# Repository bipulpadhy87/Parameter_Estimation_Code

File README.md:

# Complex-receiver inductance estimator

Revision: 2026-09-26

**Before enabling identification, set the actual installed primary and
secondary compensation capacitances.** Both remain `0UL` by default, as in the
supplied firmware; zero capacitance intentionally prevents a valid result.
Do not substitute the simulation's values for hardware measurements.

Also enter/verify the actual primary bridge voltage, effective series losses,
coil-inductance bounds, phase calibration, and uncertainty allowances. The
inherited voltage default is 5000 mV; the inherited resistance defaults are
zero. None of these defaults is a measurement of the hardware.

The numerical core uses `long double` for the slow solve. TI documents this as
64-bit for both C28x COFF and EABI; plain `double` is only 32-bit in COFF. Allow
64-bit floating-point operations in the CCS compiler settings (do not retain
`--float_operations_allowed=none` or `=32` for this translation unit). Keep
strict floating-point semantics for the NaN/finite checks. The C28x runtime
support library supplies the arithmetic. No MATLAB runtime, heap allocation,
complex-number library, or external numerical library is required.

The larger matrices use static storage. The solver is not reentrant and must
not run in an ISR. It executes in the existing paused-acquisition analysis
path after both records are collected. Primary PWM continues as before during
analysis. **Target execution time, stack/RAM/flash use, watchdog servicing and
protection behavior have NOT been measured.** Check the CCS map and profiling
results, and preserve independent hardware protection before a power test.
Start validation with appropriate low-energy, current-limited conditions;
the parameter estimator is not a protection function.

TI references for the numeric implementation:
- https://software-dl.ti.com/docs/esd/SPRU514/c28x-double-and-long-double-floating-point-types-spru5144178.html
- https://software-dl.ti.com/C2000/docs/optimization_guide/phase1/floating_point.html

## Which uploaded method was used

The basis is `parameterestimation.m` from `Parameter estimation.zip`.
An unmodified copy is included as `reference/parameterestimation_original.m`.
That script uses two **fundamental** input impedances to estimate four real
unknowns: common self-inductance L, mutual inductance M, receiver resistance Req,
and receiver reactance Xeq. Its later calculation of DC load resistance still
uses `pi^2/8`, and its DC-current calculation uses `2/pi`.

This package ports the complex-load approach and its analytic quadratic seeds,
**but does not port those DC conversions**. To retain the user's requirement
that the third harmonic participate in identification, it extends the model
to a second, independent complex receiver ratio at the third harmonic.
That extension and the multistart nonlinear optimizer are new work; they are
not an assertion that the uploaded MATLAB script already implemented them.

The alternative `doublefdoublepulse.m` was not used as the estimator core. Its
`f9_dual_asym` enforces a secondary-current zero at a phase derived from receiver
voltage and later uses bridge-waveform voltage/current conversions. Those
constraints are not appropriate for an arbitrary synchronous switching law.
`Lpestimation.m` likewise has a virtual-short assumption for its unsensed
receiver case and optional secondary measurements. No Simulink model in the
ZIP was executed or changed.

## Model and the four input impedances

The four observations, in code order, are

    Zin1(f0), Zin1(f1), Zin3(f0), Zin3(f1).

For harmonic h at operating point j:

    omega_hj = h * 2*pi * f_j
    Zp_hj = Rp + j*(omega_hj*L - 1/(omega_hj*Cp))
    Zs_hj = Rs + j*(omega_hj*L - 1/(omega_hj*Cs))
    Zin_hj = Zp_hj + (omega_hj*M)^2 / (Zs_hj + Zrec_h).

The independent fitted parameters are

    L, |M|, Rrec1, Xrec1, Rrec3, Xrec3.
    Zrec1 = Rrec1 + j*Xrec1
    Zrec3 = Rrec3 + j*Xrec3

There are eight measured real components and six fitted real parameters.
Zrec1 need not equal Zrec3. Rrec3 can be negative: these are terminal phasor
ratios under switching operation, not four independent passive linear loads.
A negative apparent third-harmonic resistance is not itself a fault.
Fundamental receiver resistance is constrained to be nonnegative; reverse
power-flow operation is outside this version.

**This model is rectifier-type independent, not assumption-free.** It can be
applied to diode or synchronous receivers when the following conditions hold:

1. For each harmonic separately, the receiver terminal ratio stays
   approximately constant between the two test frequencies:

       Zrec1(f0) approximately equals Zrec1(f1)
       Zrec3(f0) approximately equals Zrec3(f1).

   This is the essential restriction that makes identification possible.
   It is not the assumption Zrec1 = Zrec3. A receiver controller, DC voltage,
   conduction pattern or load change can violate it. The default inherited
   85/100 kHz pair is NOT certified to satisfy this restriction. Check it
   experimentally or in a trustworthy full switching model. A smaller
   frequency gap may reduce model drift but also worsens identifiability.

2. The resonant network is series-series; Lp=Ls=L. Known Cp, Cs, Rp and Rs must
   describe the actual paths. The supplied constant-loss model neglects
   frequency-dependent losses beyond those constants.

3. L and M are stable across both records and harmonics. Saturation, appreciable
   motion during collection, or changing coil geometry can violate this.

4. Input voltage/current phasors are correctly calibrated and time-aligned,
   both records are in periodic steady state, and both harmonics are strong
   enough to be measured. Receiver harmonic frequency conversion is NOT
   represented by a general harmonic-transfer matrix.

Residual and ambiguity checks cannot detect every possible model violation:
a changed receiver can sometimes imitate different coil parameters. A low
residual or a valid flag is not proof of physical truth. No claim is made that
this works for every possible synchronous controller or diode conduction mode.

## Numerical implementation

The source-script quadratic is retained for initialization, once per harmonic.
Let W=omega*1e-6 so L and M are expressed in microhenries, and let

    D_j = Re(Zin_j) - Rp
    C_j = Im(Zin_j) + 1/(omega_j*Cp)
    K = (W0/W1)^2.

Then the source's constant-complex-load constraint gives

    a = W0^2*(D0-D1)
    b = 2*(D1*W0*C0 - D0*W0^2*C1/W1)
    c = K*D0*(D1^2+C1^2) - D1*(D0^2+C0^2)
    a*L^2 + b*L + c = 0.

All in-range roots are retained. The code does not choose the first positive
root or silently return a nominal inductance when inversion fails. Near-linear
quadratics are handled separately; a cancellation-resistant quadratic formula
is used for ordinary roots.

Additional bounded grid seeds come from eliminating the receiver ratios:

    F_hj = Zin_hj - Zp_hj(L)
    A_hj = W_hj^2/F_hj
    t = M_uH^2
    Zrec_hj = t*A_hj - Zs_hj(L).

Equal receiver ratios across the frequency pair require

    t*(A_h0-A_h1) = j*(Xs_h0-Xs_h1).

A weighted least-squares solution for real t initializes M. The two
reconstructed ratios initialize each harmonic's load. These are only seeds.
The final damped Gauss-Newton iterations minimize the **forward input-impedance
errors**, using all eight real/imaginary components and analytic derivatives.

The search is finite multistart optimization, not a certified global search.
It compares materially different found candidates, rejects bound-limited or
locally weak results, and returns numerical diagnostics. It cannot prove
that an unsearched alternative solution does not exist.

## Measurement uncertainty and thresholds

The adapter computes an engineering allowance for each complex observation:

    sigma_Z = absolute_floor + relative_allowance*abs(Z)
              + sqrt(sigma_V^2 + abs(Z)^2*sigma_I^2)/abs(I).

These are editable settings in `psfbpcmc_user_settings.h`. The supplied defaults
are starting allowances, not characterized ADC/sensor statistics. The
linearized L/M sensitivity is obtained from the local weighted Jacobian and
these allowances; it is not a guaranteed accuracy or confidence interval.
Systematic phase, winding-loss, capacitance and model errors are not fully
represented by these numbers. Do not enlarge allowances simply to suppress
faults or to force an estimate to be accepted.

Default checks include normalized residual RMS <= 3, relative L/M sensitivity
<= 20%, and the inherited additional absolute residual ceiling of 5 ohms.
A second found candidate within four normalized squared-error units and
separated by over 1% in L or 2% in M triggers the ambiguity flag. These are
engineering acceptance rules, not universal statistical thresholds.

## CCS Expressions / outputs

Always inspect `WPT_identificationValid` before using the fitted values.
The solver can expose a rejected candidate's values for diagnosis; they are
not valid measurements when that flag is zero.

| Variable | Meaning / units |
|---|---|
| `WPT_estimatedSelfInductanceNanoHenry` | Common Lp=Ls, nH |
| `WPT_estimatedMutualInductanceNanoHenry` | Magnitude of M, nH |
| `WPT_estimatedCouplingPermille` | 1000*abs(M)/L |
| `WPT_estimatedEquivalentAcLoadMilliOhm` | Fundamental Rrec1, mOhm; legacy name retained |
| `WPT_estimatedEquivalentAcReactanceMilliOhm` | Fundamental Xrec1, signed mOhm |
| `WPT_estimatedThirdAcResistanceMilliOhm` | Third-harmonic Rrec3, signed mOhm |
| `WPT_estimatedThirdAcReactanceMilliOhm` | Third-harmonic Xrec3, signed mOhm |
| `WPT_identificationResidualMilliOhm` | Unweighted RMS across eight components, mOhm |
| `WPT_identificationNormalizedResidualPermille` | 1000 * weighted RMS |
| `WPT_identificationLRelativeSensitivityPermille` | 1000 * local relative L sensitivity |
| `WPT_identificationMRelativeSensitivityPermille` | 1000 * local relative M sensitivity |
| `WPT_identificationImpedanceSigmaMilliOhm[4]` | Per-observation engineering uncertainty, mOhm |
| `WPT_identificationSolverFlags` | Bitmask described below; 0 means checks passed |
| `WPT_identificationSolutionsChecked` | Number of multistart results checked |
| `WPT_identificationAlternativeSelfInductanceNanoHenry` | Found alternative L when ambiguous |
| `WPT_identificationAlternativeMutualInductanceNanoHenry` | Found alternative M when ambiguous |
| `WPT_identificationModelWarning` | Stays 1 after every solve: modeling assumptions remain |
| `WPT_estimatedDcLoadValid` | Always 0; no DC load estimate is available |
| `WPT_estimatedDcLoadMilliOhm` | Always invalid sentinel 0xFFFFFFFF, never a resistance |

Flag bits may be combined:

| Bit value | Meaning |
|---:|---|
| 1 | Invalid configuration/input |
| 2 | No physically acceptable seeded solution |
| 4 | Excessive fit residual |
| 8 | Materially different, similarly compatible solutions found |
| 16 | Weak local L/M identifiability or singular sensitivity calculation |
| 32 | Result at an inductance/coupling bound |
| 64 | Required third-harmonic record missing |
| 128 | Invalid/too-small phasor or guarded arithmetic range |

Set `WPT_identificationResetRequest=1` to start another experiment, as before.
Read the two existing input-impedance arrays for the fundamental and the two
third-harmonic arrays to see the actual four observations supplied to the fit.
No secondary current sensor or secondary telemetry was added.

## PWM, dead time and acquisition

The existing acquisition rate, ADC configuration, harmonic extraction,
automatic case-7 to case-5 transition, PWM setup, phase values, blanking, and
trip handling are retained. In particular, case 7 retains **PH_1_4=586**.
Seventeen existing functions were compared after removing comments and
whitespace; their executable source is unchanged.

Primary voltage reconstruction still uses actual configured PWM timing,
primary dead time and current-dependent clamp polarity. The only executable
change in that reconstruction function permits zero source V3 when a usable
I3 is present; it no longer unnecessarily rejects that observation. The
dead-time arithmetic itself is unchanged.

That voltage reconstruction still neglects Coss, driver propagation delays,
diodes' finite voltage drops and ringing. Measured primary voltage phasor
overrides remain available. No receiver-side PWM phase or diode waveform is
used to calculate the receiver ratios.

## Validation actually performed

These checks are included as code/results in `tests/`:

- Estimator core compiled with GCC C99, `-Wall -Wextra -Werror`, using host
  long double and an explicit 64-bit double configuration.
- Five noiseless synthetic model cases: resistive fundamental load, reactive
  load, negative third-harmonic resistance, strong coupling, and different
  fundamental/third loads. Parameter recovery matched the constructed models
  to numerical precision. This is algebra/software validation, not evidence
  about a real rectifier.
- Analytic Jacobian checked against independent NumPy finite differences.
- Invalid capacitance/frequency/noise settings, NaNs, weak coupling, selected
  receiver changes and corrupt observations tested. Rejected results clear
  stale valid outputs. This does not claim all receiver changes are detectable.
- Forty randomized exact-model cases and forty noisy cases with fixed seed
  260926. All passed the stated test assertions. In the noisy test, each
  impedance component had 0.01-ohm Gaussian noise and the largest L/M errors
  were approximately 0.157% / 0.209% for that one chosen synthetic system.
- The same core tests ran under GCC's undefined-behavior sanitizer.
- The actual new adapter was extracted from the revised main.c and compiled
  with the actual updated settings/header. With quantized synthetic mV/mA
  phasors, true L=180 uH and M=130 uH produced L=179.799 uH and M=129.783 uH;
  the input-impedance RMS residual was 44 mOhm. DC validity stayed false.
- Default zero capacitor settings, missing third data, zero third current,
  oversized phasors and repeated frequencies failed closed in adapter tests.
- Regression comparison confirmed the preserved executable functions and
  case-7 phase correction.

**NOT performed:** full TI CCS compilation/linking, real-time timing or stack
profiling on the F280049C, MATLAB/Simulink execution, time-domain diode or
synchronous-rectifier simulation, sensor calibration, or hardware testing.
Do not interpret the synthetic tests as verification of arbitrary receivers.

To rerun the portable tests, install Python 3, NumPy and a C99 GCC compiler:

    python tests/test_estimator.py
    python tests/test_integration.py
    python tests/test_extended.py

The preservation test additionally needs the unmodified pre-change firmware:

    python tests/test_preservation.py /path/to/original/directory

Test binaries are intentionally not included. Generated `tests/build/` files
are host-test artifacts, not CCS project sources.

## Package contents

The three firmware files are at the package root. Two unified `.patch` files
show changes against the supplied original main/settings files. `reference/`
contains the unmodified chosen MATLAB script. `tests/` contains test sources
and recorded JSON results. No source Library file or original ZIP was modified.

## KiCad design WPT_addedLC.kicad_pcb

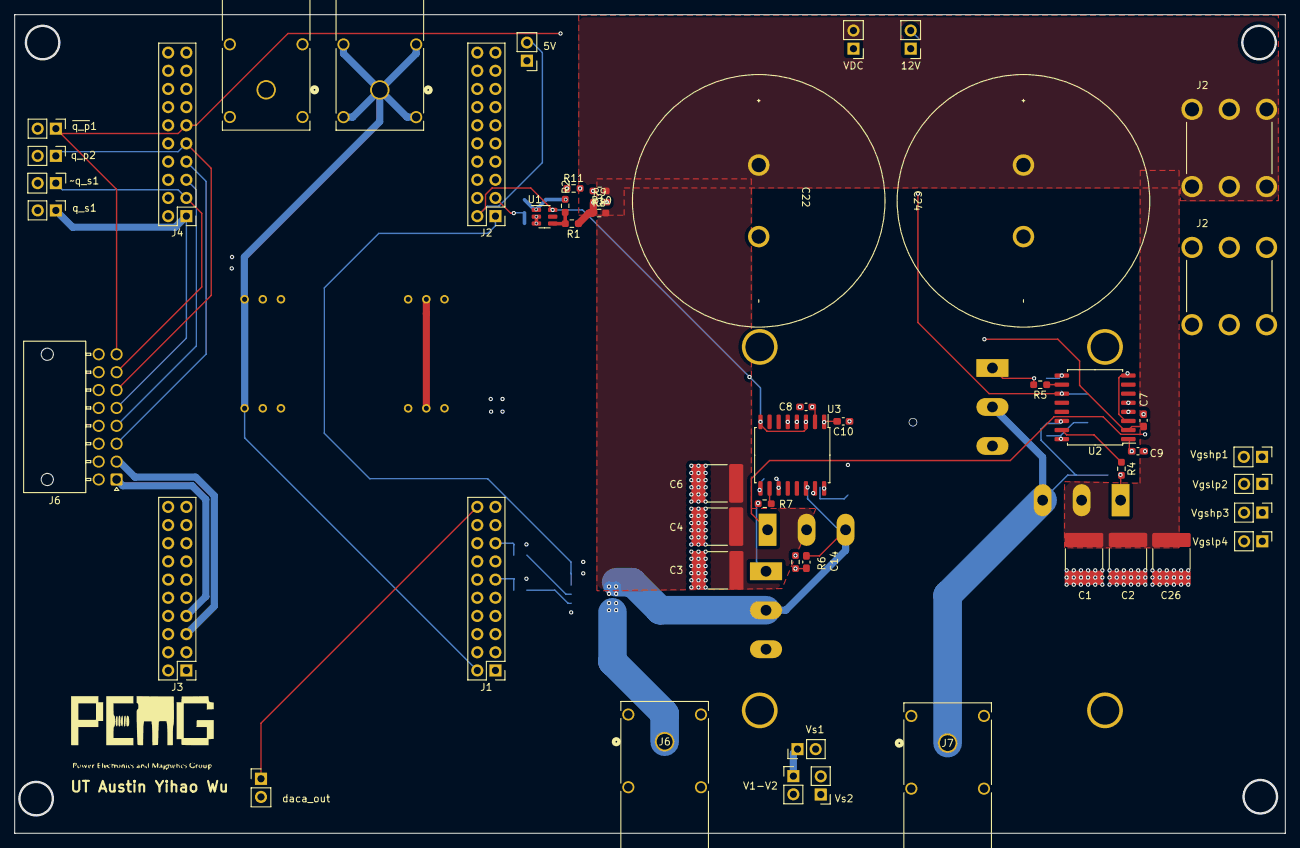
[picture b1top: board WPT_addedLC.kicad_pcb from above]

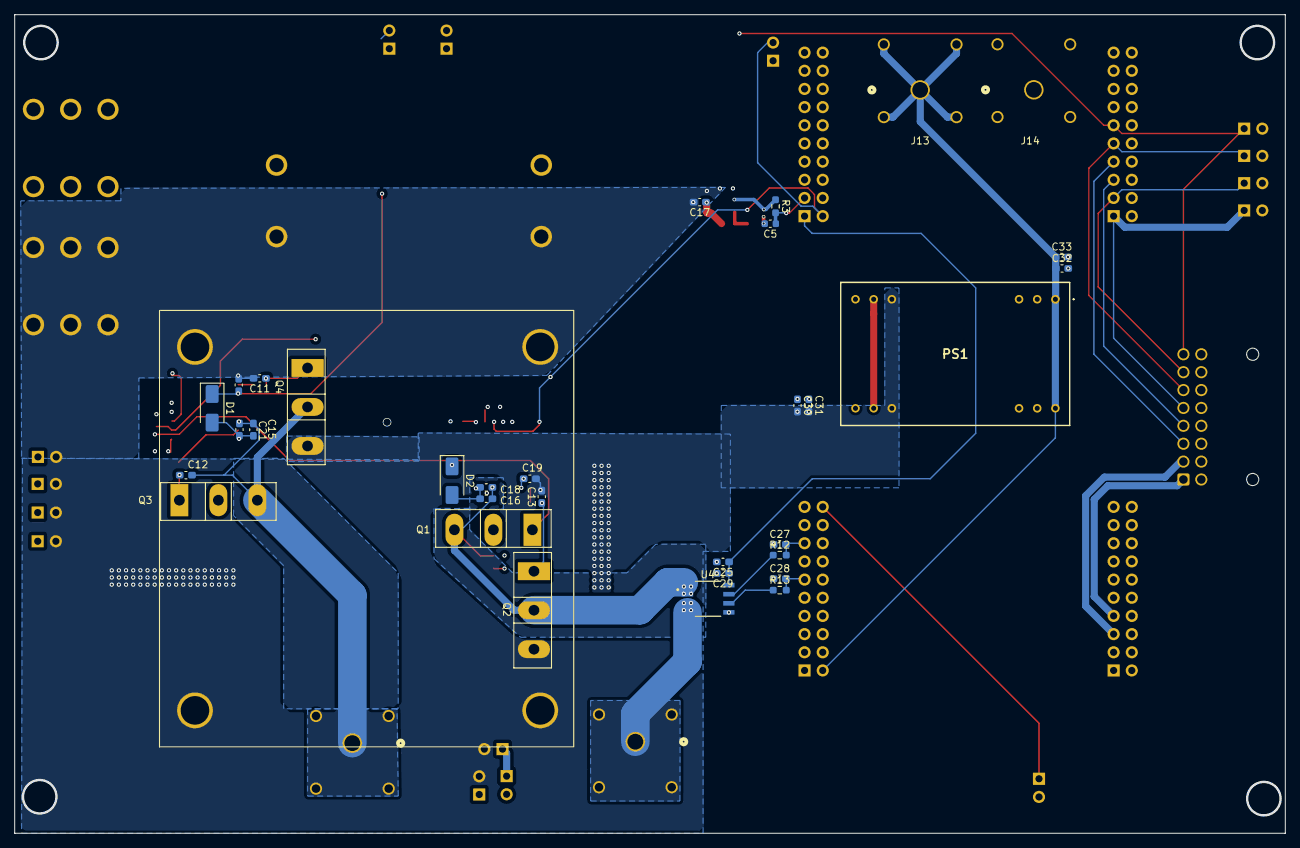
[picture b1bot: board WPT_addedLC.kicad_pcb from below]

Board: 4 copper layers, 177.6 x 114.4 mm, 80 parts (30 on the bottom side), 36 nets.

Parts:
5V, 12V: TP_Header; PinHeader_1x02_P2.54mm_Vertical
C1, C2, C3, C4, C6, C26: C_Small; C_2220_5750Metric_Pad1.97x5.40mm_HandSolder
C5: 1nf; C_0603_1608Metric
C7, C8, C9, C10, C11, C12, C13, C14, C15, C16, C17, C18, C19, C20, C21: C_Small; C_0603_1608Metric_Pad1.08x0.95mm_HandSolder
C22, C24: 1mF; CP_Elec_dia1in
C25, C31, C32: 0.1u; C_0603_1608Metric_Pad1.08x0.95mm_HandSolder
C27, C28: 100p; C_0603_1608Metric_Pad1.08x0.95mm_HandSolder
C29, C30, C33: 1u; C_0603_1608Metric_Pad1.08x0.95mm_HandSolder
D1, D2: D_SMA
J1, J2#2, J3, J4: Conn_02x10_Row_Letter_First; PinHeader_2x10_P2.54mm_Vertical_LetterNumber
J2, J2#3: Conn_01x01_Pin; KEYSTONE_7808
J6, J7, J13, J14: FCR7350R; CONN1_FCR7350R_CLF
J6#2: Conn_02x08_Odd_Even; Molex_Nano-Fit_105314-xx16_2x08_P2.50mm_Horizontal
PS1: TEL_3-0512; TEL30522
Q1, Q2, Q3, Q4: C3M0065090D; TO-247-3_Vertical
R1, R2, R8, R9, R10, R11: 10k7; R_0603_1608Metric_Pad0.98x0.95mm_HandSolder
R3: 100; R_0603_1608Metric_Pad0.98x0.95mm_HandSolder
R4, R5, R6, R7: 10; R_0603_1608Metric_Pad0.98x0.95mm_HandSolder
R12, R13: 49.9; R_0603_1608Metric_Pad0.98x0.95mm_HandSolder
U1: TLV2470; SOT-23-6
U2, U3: ADuM3223; SOIC-16W_7.5x10.3mm_P1.27mm
U4: ACS37030LLZATR-020B3; IC_ACS37030LLZATR-020B3
V1-V2: TP_Header; PinHeader_1x02_P2.54mm_Vertical
VDC: TP_Header; PinHeader_1x02_P2.54mm_Vertical
Vgshp1, Vgshp3: TP_Header; PinHeader_1x02_P2.54mm_Vertical
Vgslp2, Vgslp4: TP_Header; PinHeader_1x02_P2.54mm_Vertical
Vs1, Vs2: TP_Header; PinHeader_1x02_P2.54mm_Vertical
daca_out: TP_Header; PinHeader_1x02_P2.54mm_Vertical
q_p2: TP_Header; PinHeader_1x02_P2.54mm_Vertical
q_s1: TP_Header; PinHeader_1x02_P2.54mm_Vertical

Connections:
/3.3V: C25.1, C29.1, J2#2.a1, U4.6 (VDD)
/5V_uC: 5V.2, C32.1, C33.1, J1.b1, J2#2.b1, J13.1 (1_1), J13.2, J13.3, J13.4, J13.5, PS1.1 (+VIN_(VCC)_1), PS1.24 (+VIN_(VCC)_2), U1.6 (VDD), U2.3 (VDD1), U2.8 (VDD1), U3.3 (VDD1), U3.8 (VDD1)
/+12V: 12V.2, C19.1, C20.1, C30.1, C31.1, D1.1 (A), D2.1 (A), PS1.11 (+VOUT_1), PS1.14 (+VOUT_2), U2.11 (V_{DDB}), U3.11 (V_{DDB})
/Iout2_adc: C28.2, J1.a6, R13.2
/Iout_adc: C27.2, J1.a8, R12.2
/Vcurrent2: J6.1 (1_1), J6.2, J6.3, J6.4, J6.5, U4.2 (IP-)
/Vdc: C1.1, C2.1, C3.1, C4.1, C6.1, C22.1, C24.1, C26.1, J2#3.1_1, J2#3.1_2, J2#3.1_3, J2#3.1_4, J2#3.1_5, J2#3.1_6, Q1.2 (D), Q3.2 (D), R8.2, R10.2, VDC.2
/Vgshp1: C14.1, Q1.1 (G), R6.2, Vgshp1.1
/Vgshp3: C12.1, Q3.1 (G), R4.2, Vgshp3.1
/Vgslp2: C13.1, Q2.1 (G), R7.2, Vgslp2.1
/Vgslp4: C11.1, Q4.1 (G), R5.2, Vgslp4.1
/Vout_adc: C5.1, J2#2.a2, R3.2
/Vout_low: C17.1, R1.1, R8.1, R9.2
/Vs1: C14.2, C16.2, C18.1, Q1.3 (S), Q2.2 (D), U3.14 (GND_{A}), U4.1 (IP+), V1-V2.1, Vs1.1
/Vs2: C12.2, C15.2, C21.1, J7.1 (1_1), J7.2, J7.3, J7.4, J7.5, Q3.3 (S), Q4.2 (D), U2.14 (GND_{A}), V1-V2.2, Vs2.1
/daca_out: J1.b10, daca_out.1
/q_p: C9.2, J4.a5, J6#2.6, U2.1 (V_{1A}), q_p2.1
/q_s: C10.2, J4.a1, J6#2.5, U3.1 (V_{1A}), q_s1.1
/q_sh1: J4.a3, J6#2.4
/q_sh2: J3.a3, J6#2.2
/~q_p: C7.1, J4.a6, J6#2.8, U2.2 (V_{IB})
/~q_sh1: J4.a4, J6#2.3
/~q_sh2: J3.a4, J6#2.1
/~q_s: C8.1, J4.a2, J6#2.7, U3.2 (V_{IB})
Earth: 12V.1, C1.2, C2.2, C3.2, C4.2, C6.2, C11.2, C13.2, C17.2, C19.2, C20.2, C22.2, C24.2, C26.2, C30.2, C31.2, J2.1_1, J2.1_2, J2.1_3, J2.1_4, J2.1_5, J2.1_6, PS1.10 (COMMON_2), PS1.15 (COMMON_3), Q2.3 (S), Q4.3 (S), R9.1, R10.1, R11.2, U2.9 (GND_{B}), U3.9 (GND_{B}), VDC.1, Vgshp1.2, Vgshp3.2, Vgslp2.2, Vgslp4.2, Vs1.2, Vs2.2
GND: 5V.1, C5.2, C7.2, C8.2, C9.1, C10.1, C25.2, C27.1, C28.1, C29.2, C32.2, C33.2, J1.a5, J1.a7, J1.b2, J1.b5, J1.b6, J1.b7, J2#2.b2, J3.b1, J4.b1, J6#2.9, J6#2.10, J6#2.11, J6#2.12, J6#2.13, J6#2.14, J6#2.15, J6#2.16, J14.1 (1_1), J14.GND, PS1.12 (-VIN_(GND)_1), PS1.13 (-VIN_(GND)_2), R11.1, U1.2 (GND), U1.3 (IN+), U2.4 (GND1), U2.5 (DISABLE), U3.4 (GND1), U3.5 (DISABLE), U4.3 (GND), daca_out.2, q_p2.2, q_s1.2
unnamed: C15.1, C21.2, D1.2 (K), U2.16 (V_{DDA})
unnamed: C16.1, C18.2, D2.2 (K), U3.16 (V_{DDA})
unnamed: R1.2, R2.1, U1.4 (IN-)
unnamed: R2.2, R3.1, U1.1 (OUT)
unnamed: R4.1, U2.15 (V_{OA})
unnamed: R5.1, U2.10 (V_{OB})
unnamed: R6.1, U3.15 (V_{OA})
unnamed: R7.1, U3.10 (V_{OB})
unnamed: R12.1, U4.5 (VOUT)
unnamed: R13.1, U4.4 (VREF)
